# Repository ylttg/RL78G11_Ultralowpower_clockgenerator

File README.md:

# RL78G11_Ultralowpower_clockgenerator
Clock generator hardware / software design using RL78/G11

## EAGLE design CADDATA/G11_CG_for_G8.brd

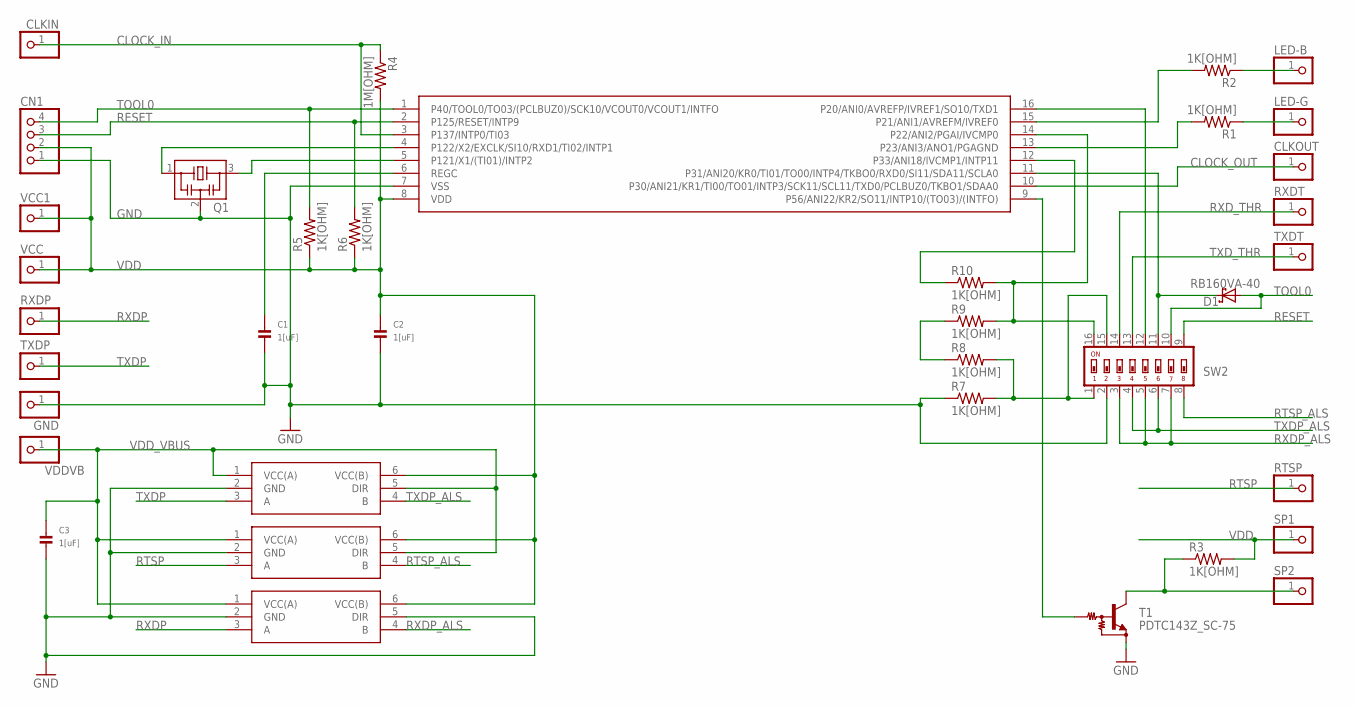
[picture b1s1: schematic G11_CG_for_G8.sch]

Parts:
C1, C2, C3: 1[uF]; _0603
CLKIN: PINHD-1X1; 1X01
CLKOUT: PINHD-1X1; 1X01
CN1: PINHD-1X4; 1X04
D1: RB160VA-40; TUMD2
GND: PINHD-1X1; 1X01
LED-B: PINHD-1X1; 1X01
LED-G: PINHD-1X1; 1X01
Q1: CSTNE
R1, R2, R3, R5, R6, R7, R8, R9, R10: 1K[OHM]; R0603
R4: 1M[OHM]; R0603
RTSP: PINHD-1X1; 1X01
RXDP: PINHD-1X1; 1X01
RXDT: PINHD-1X1; 1X01
SP1, SP2: PINHD-1X1; 1X01
SW2: SWS008; SMS-008
T1: PDTC143Z_SC-75; SC-75
TXDP: PINHD-1X1; 1X01
TXDT: PINHD-1X1; 1X01
U1: RL78/G11_SSOP16; SSOP16_(4.4X5.0)
U2, U3, U4: 74LVC1T45W6; SOT-26
VCC, VCC1: PINHD-1X1; 1X01
VDDVB: PINHD-1X1; 1X01

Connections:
CLOCK_IN: CLKIN.1, R4.1, U1.3 (P137/INTP0/TI03)
CLOCK_OUT: CLKOUT.1, U1.10 (P30/ANI21/KR1/TI00/TO01/INTP3/SCK11/SCL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)
GND: C1.2, C2.2, C3.2, CN1.1, GND.1, Q1.2, R7.1, SW2.2, T1.2 (E), U1.7 (VSS), U2.2 (GND), U3.2 (GND), U4.2 (GND), U4.5 (DIR)
unnamed: R3.1, SP2.1, T1.3 (C)
unnamed: T1.1 (B), U1.9 (P56/ANI22/KR2/SO11/INTP10/(TO03)/(INTFO))
unnamed: LED-B.1, R2.1
unnamed: LED-G.1, R1.1
unnamed: R1.2, U1.13 (P23/ANI3/ANO1/PGAGND)
unnamed: Q1.3, U1.5 (P121/X1/(TI01)/INTP2)
unnamed: R2.2, U1.15 (P21/ANI1/AVREFM/IVREF0)
unnamed: Q1.1, U1.4 (P122/X2/EXCLK/SI10/RXD1/TI02/INTP1)
unnamed: C1.1, U1.6 (REGC)
unnamed: R9.2, R10.2, SW2.16, U1.14 (P22/ANI2/PGAI/IVCMP0)
unnamed: SW2.12, U1.16 (P20/ANI0/AVREFP/IVREF1/SO10/TXD1)
unnamed: R8.1, R9.1
unnamed: R7.2, R8.2, SW2.1, SW2.15
unnamed: R10.1, U1.12 (P33/ANI18/IVCMP1/INTP11)
unnamed: D1.P$1 (C), SW2.11, U1.11 (P31/ANI20/KR0/TI01/TO00/INTP4/TKBO0/RXD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)
RESET: CN1.3, R6.2, SW2.9, U1.2 (P125/RESET/INTP9)
RTSP: RTSP.1, U3.3 (A)
RTSP_ALS: SW2.8, U3.4 (B)
RXDP: RXDP.1, U4.3 (A)
RXDP_ALS: SW2.3, SW2.5, SW2.7, U4.4 (B)
RXD_THR: RXDT.1, SW2.14
TOOL0: CN1.4, D1.P$2 (A), R5.2, SW2.10, U1.1 (P40/TOOL0/TO03/(PCLBUZ0)/SCK10/VCOUT0/V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)
TXDP: TXDP.1, U2.3 (A)
TXDP_ALS: SW2.4, SW2.6, U2.4 (B)
TXD_THR: SW2.13, TXDT.1
VDD: C2.1, CN1.2, R3.2, R4.2, R5.1, R6.1, SP1.1, U1.8 (VDD), U2.6 (VCC(B)), U3.6 (VCC(B)), U4.6 (VCC(B)), VCC.1, VCC1.1
VDD_VBUS: C3.1, U2.1 (VCC(A)), U2.5 (DIR), U3.1 (VCC(A)), U3.5 (DIR), U4.1 (VCC(A)), VDDVB.1

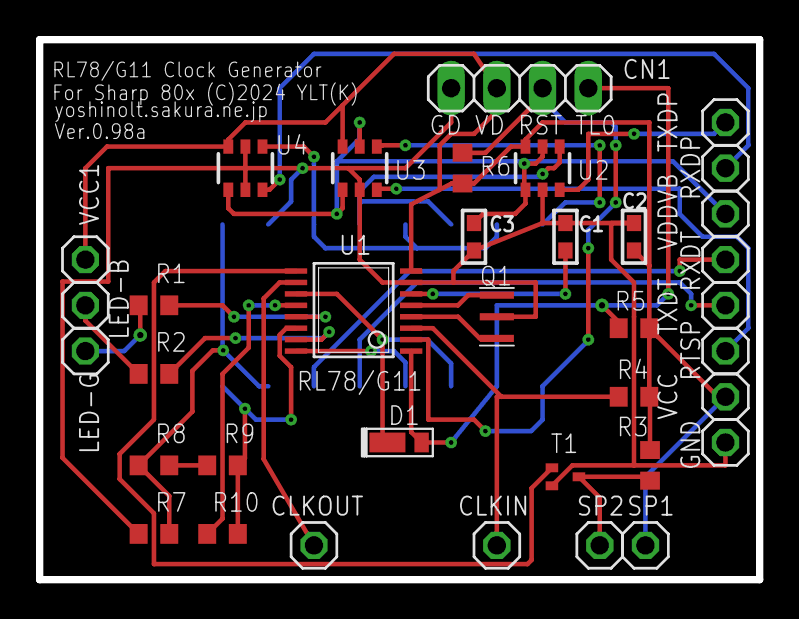
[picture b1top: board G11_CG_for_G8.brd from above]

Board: 2 copper layers, 40.0 x 30.0 mm, 37 parts (1 on the bottom side), 30 nets.

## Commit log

2024-10-30 Add files via upload
    This is first edition that supports our clock generator

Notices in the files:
CADDATA/G11_CG_for_G8.brd:
For Sharp 80x (C)2024 YLT(K)
parts and their libraries:
microbuilder: This work is placed in the public domain, and may be freely used for commercial and non-commercial work with the following conditions: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
